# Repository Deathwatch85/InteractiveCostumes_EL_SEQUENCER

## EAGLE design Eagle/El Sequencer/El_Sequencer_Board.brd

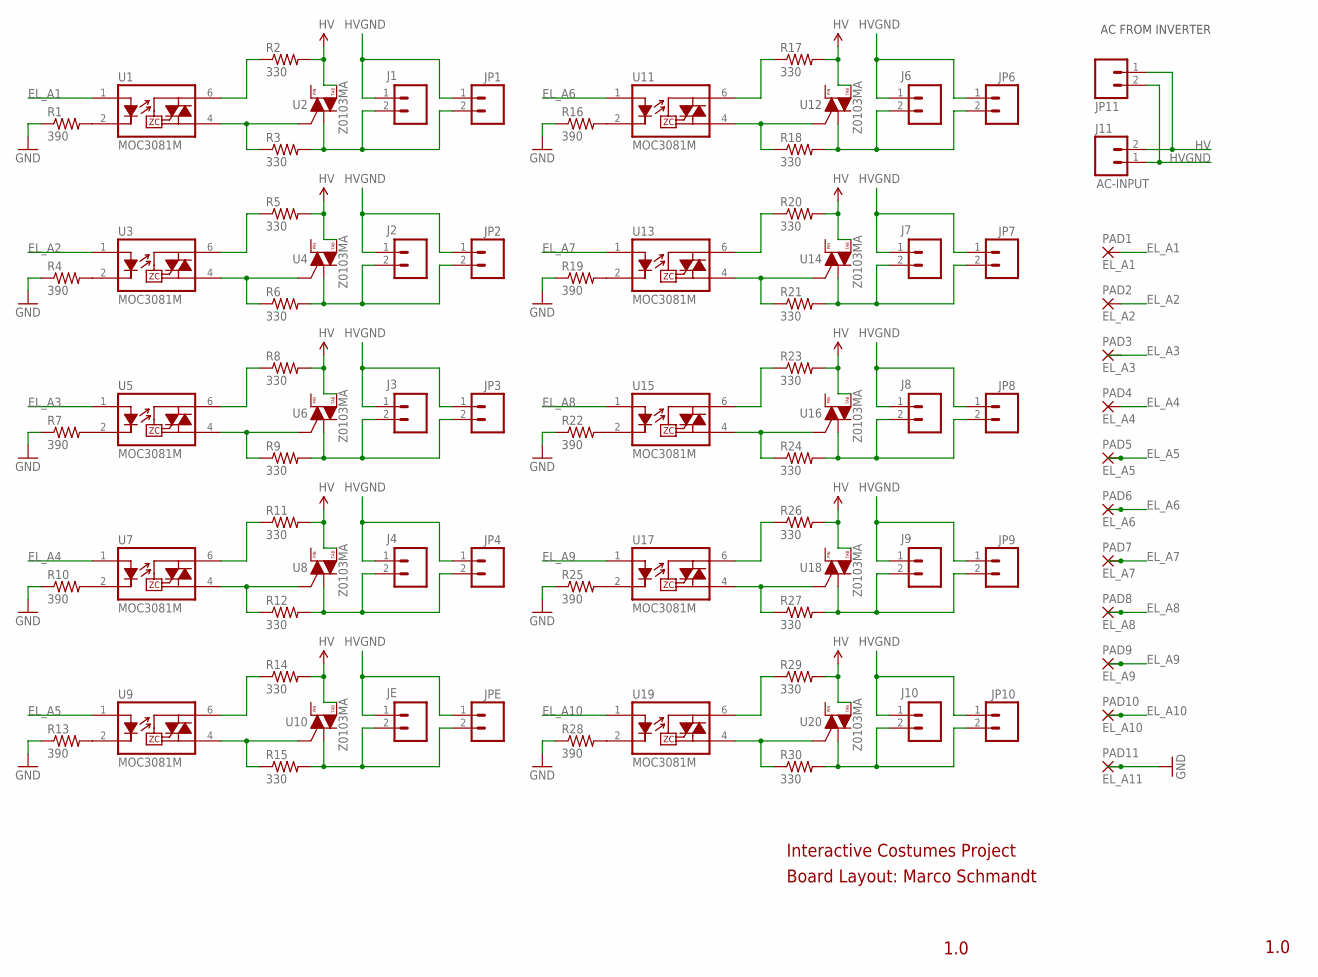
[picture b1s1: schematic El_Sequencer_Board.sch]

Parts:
J1, J2, J3, J4, J6, J7, J8, J9, J10: M02-JST-2MM-SMT; JST-2-SMD
J11: AC-INPUT; JST-2-SMD
JE: M02-JST-2MM-SMT; JST-2-SMD
JP1, JP2, JP3, JP4, JP6, JP7, JP8, JP9, JP10, JP11: M02PTH; 1X02
JPE: M02PTH; 1X02
PAD1: EL_A1; 5-2,5
PAD2: EL_A2; 5-2,5
PAD3: EL_A3; 5-2,5
PAD4: EL_A4; 5-2,5
PAD5: EL_A5; 5-2,5
PAD6: EL_A6; 5-2,5
PAD7: EL_A7; 5-2,5
PAD8: EL_A8; 5-2,5
PAD9: EL_A9; 5-2,5
PAD10: EL_A10; 5-2,5
PAD11: EL_A11; 5-2,5
R1, R4, R7, R10, R13, R16, R19, R22, R25, R28: 390; 0402-RES
R2, R3, R5, R6, R8, R9, R11, R12, R14, R15, R17, R18, R20, R21, R23, R24, R26, R27, R29, R30: 330; 0603-RES
U1, U3, U5, U7, U9, U11, U13, U15, U17, U19: MOC3081M; DIP8SMD
U2, U4, U6, U8, U10, U12, U14, U16, U18, U20: Z0103MA; SOT223

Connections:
EL_A1: PAD1.1, U1.1 (A)
EL_A2: PAD2.1, U3.1 (A)
EL_A3: PAD3.1, U5.1 (A)
EL_A4: PAD4.1, U7.1 (A)
EL_A5: PAD5.1, U9.1 (A)
EL_A6: PAD6.1, U11.1 (A)
EL_A7: PAD7.1, U13.1 (A)
EL_A8: PAD8.1, U15.1 (A)
EL_A9: PAD9.1, U17.1 (A)
EL_A10: PAD10.1, U19.1 (A)
GND: PAD11.1, R1.1, R4.1, R7.1, R10.1, R13.1, R16.1, R19.1, R22.1, R25.1, R28.1
HV: J11.2, JP11.1, R2.2, R5.2, R8.2, R11.2, R14.2, R17.2, R20.2, R23.2, R26.2, R29.2, U2.4 (T2), U4.4 (T2), U6.4 (T2), U8.4 (T2), U10.4 (T2), U12.4 (T2), U14.4 (T2), U16.4 (T2), U18.4 (T2), U20.4 (T2)
HVGND: J1.1, J2.1, J3.1, J4.1, J6.1, J7.1, J8.1, J9.1, J10.1, J11.1, JE.1, JP1.1, JP2.1, JP3.1, JP4.1, JP6.1, JP7.1, JP8.1, JP9.1, JP10.1, JP11.2, JPE.1
unnamed: R6.1, U3.4 (T2), U4.3 (G)
unnamed: R4.2, U3.2 (K)
unnamed: R5.1, U3.6 (T1)
unnamed: J2.2, JP2.2, R6.2, U4.1 (T1)
unnamed: R9.1, U5.4 (T2), U6.3 (G)
unnamed: R7.2, U5.2 (K)
unnamed: R8.1, U5.6 (T1)
unnamed: J3.2, JP3.2, R9.2, U6.1 (T1)
unnamed: R12.1, U7.4 (T2), U8.3 (G)
unnamed: R10.2, U7.2 (K)
unnamed: R11.1, U7.6 (T1)
unnamed: J4.2, JP4.2, R12.2, U8.1 (T1)
unnamed: R15.1, U9.4 (T2), U10.3 (G)
unnamed: R13.2, U9.2 (K)
unnamed: R14.1, U9.6 (T1)
unnamed: JE.2, JPE.2, R15.2, U10.1 (T1)
unnamed: R18.1, U11.4 (T2), U12.3 (G)
unnamed: R16.2, U11.2 (K)
unnamed: R17.1, U11.6 (T1)
unnamed: J6.2, JP6.2, R18.2, U12.1 (T1)
unnamed: R21.1, U13.4 (T2), U14.3 (G)
unnamed: R3.1, U1.4 (T2), U2.3 (G)
unnamed: R1.2, U1.2 (K)
unnamed: R2.1, U1.6 (T1)
unnamed: J1.2, JP1.2, R3.2, U2.1 (T1)
unnamed: R19.2, U13.2 (K)
unnamed: R20.1, U13.6 (T1)
unnamed: J7.2, JP7.2, R21.2, U14.1 (T1)
unnamed: R24.1, U15.4 (T2), U16.3 (G)
unnamed: R22.2, U15.2 (K)
unnamed: R23.1, U15.6 (T1)
unnamed: J8.2, JP8.2, R24.2, U16.1 (T1)
unnamed: R27.1, U17.4 (T2), U18.3 (G)
unnamed: R25.2, U17.2 (K)
unnamed: R26.1, U17.6 (T1)
unnamed: J9.2, JP9.2, R27.2, U18.1 (T1)
unnamed: R30.1, U19.4 (T2), U20.3 (G)
unnamed: R28.2, U19.2 (K)
unnamed: R29.1, U19.6 (T1)
unnamed: J10.2, JP10.2, R30.2, U20.1 (T1)

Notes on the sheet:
AC FROM INVERTER
Interactive Costumes Project
Board Layout: Marco Schmandt
1.0

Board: 2 copper layers, 83 parts (0 on the bottom side), 53 nets, no tracks yet.

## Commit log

2014-07-14 added necessary files for setup
2014-07-14 added folders for code and eagle files
2014-07-22 added final version of el wire code
2014-07-22 first version of the code for the oxygen tank
2014-07-22 added circuit diagram of used prototype configuration of el sequencer
2014-07-22 Create gh-pages branch via GitHub
2014-07-22 created a temporary site
2014-07-22 modified site
2014-07-23 updated lincense file
2014-07-30 fixed issue with buttonCounter
2014-08-15 new README.md
2015-01-31 added EAGLE files

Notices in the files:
parts and their libraries:
SparkFun-Aesthetics: Licensing: Creative Commons ShareAlike 4.0 International - https://creativecommons.org/licenses/by-sa/4.0
